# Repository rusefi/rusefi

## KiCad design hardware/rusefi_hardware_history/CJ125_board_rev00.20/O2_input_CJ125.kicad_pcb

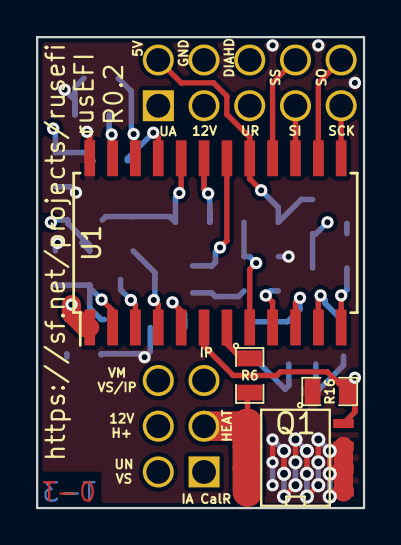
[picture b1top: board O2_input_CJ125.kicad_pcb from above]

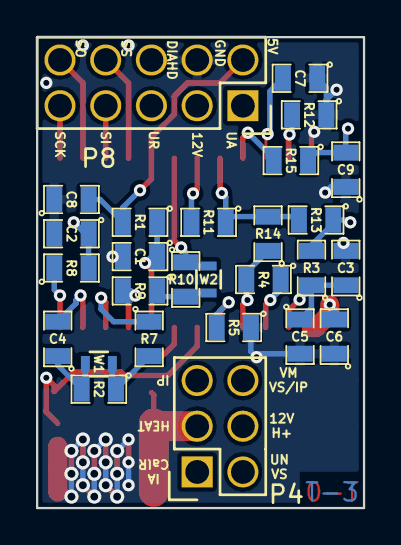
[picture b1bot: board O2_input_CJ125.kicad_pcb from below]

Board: 4 copper layers, 18.2 x 26.2 mm, 31 parts (27 on the bottom side), 31 nets.

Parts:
C1: 1000pF; SM0805
C2, C6, C8: 0.033uF; SM0805
C3, C4, C7: 0.1uF; SM0805
C5: 220pf; SM0805
C9: 0.01uF; SM0805
P4: CONN_02X03; Socket_Strip_Straight_2x03
P8: CONN_02X05; Socket_Strip_Straight_2x05
Q1: FDS2734; SO8E_ST
R1, R5, R7, R16: 10k; SM0805
R2: 21k6; SM0805
R3: 160; SM0805
R4: 61.9; SM0805
R6: 6.8k; SM0805
R8, R15: 1k; SM0805
R9: 82.5; SM0805
R10: 117.5; SM0805
R11: 4.7k; SM0805
R12, R13: 100k; SM0805
R14: 470k; SM0805
U1: CJ125; SOIC-24_7.5x15.4mm_Pitch1.27mm
W1, W2: TEST; R_0603

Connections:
/CF: C7.2, U1.22
/CJ125_5v: C8.2, P8.2, R1.2, U1.17
/CJ125_HEATER: P4.3, Q1.2, R6.2
/CJ125_IA: P4.1, R4.2, R14.1, U1.4
/CJ125_IP: P4.5, R4.1, U1.3
/CJ125_SCK: P8.9, U1.13
/CJ125_SI: P8.7, U1.15
/CJ125_SO: P8.10, U1.14
/CJ125_SS: P8.8, U1.16
/CJ125_UA: C9.2, P8.1, R15.1
/CJ125_UN: P4.2, R3.2, R13.1
/CJ125_UR: C2.1, P8.5, R8.2
/CJ125_VM: P4.6, R10.1, U1.18, W2.2
/CM: C4.2, U1.11
/DIAHD: R6.1, U1.7
/DIAHG: P8.6, Q1.1, R16.2, U1.6
/OSZ: R5.2, U1.5
/RF: R12.2, U1.23
/RM: R7.1, U1.10
/RS: R9.2, U1.9
/RST: C1.1, R1.1, U1.8
/UA: R15.2, U1.21
/UN: C3.1, C5.1, R3.1, U1.2
/UP: R11.1, R13.2, R14.2, U1.20
/UR: R8.1, U1.12
/US: R11.2, U1.19
/WO2-12V: C6.2, P4.4, P8.3, U1.1
GND: C1.2, C2.2, C3.2, C5.2, C6.1, C7.1, C8.1, C9.1, P8.4, Q1.3, R5.1, R12.1, R16.1, U1.24
unnamed: C4.1, R2.2, W1.1
unnamed: R2.1, R7.2, W1.2
unnamed: R9.1, R10.2, W2.1

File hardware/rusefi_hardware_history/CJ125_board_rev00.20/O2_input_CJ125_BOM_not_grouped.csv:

Reference, Value, Footprint, Datasheet, mfg,mfg#, vend1,vend1#
C7,0.1uF,SM0805,,avx,08055C104KAT2A,DIGI,478-1395-1-ND
R15,1k,SM0805,,Panasonic,ERA-6AEB102V,DIGI,P1.0KDACT-ND
R13,100k,SM0805,,vishay,CRCW0805100KFKEA,DIGI,541-100KCCT-ND
C9,0.01uF,SM0805,,avx,08055C103JAT2A,DIGI,478-3745-6-ND
C6,0.033uF,SM0805,,tdk,CGA4J2C0G1H333J125AA,DIGI,445-6950-1-ND
R8,1k,SM0805,,Panasonic,ERA-6AEB102V,DIGI,P1.0KDACT-ND
R4,61.9,SM0805,,vishay,CRCW080561R9FKEA,DIGI,541-61.9CCT-ND
R5,10k,SM0805,,BOURNS,CR0805-FX-1002ELF,DIGI,CR0805-FX-1002ELFCT-ND
C2,0.033uF,SM0805,,tdk,CGA4J2C0G1H333J125AA,DIGI,445-6950-1-ND
R12,100k,SM0805,,vishay,CRCW0805100KFKEA,DIGI,541-100KCCT-ND
C1,1000pF,SM0805,,avx,08052C102KAT2A ,DIGI,478-1339-1-ND
R6,6.8k,SM0805,,vishay,CRCW08056K80FKEA,DIGI,541-6.80KCCT-ND
C5,220pf,SM0805,,avx,08051A221JAT2A,DIGI,478-1286-1-ND
R1,10k,SM0805,,BOURNS,CR0805-FX-1002ELF,DIGI,CR0805-FX-1002ELFCT-ND
C4,0.1uF,SM0805,,avx,08055C104KAT2A,DIGI,478-1395-1-ND
R7,10k,SM0805,,BOURNS,CR0805-FX-1002ELF,DIGI,CR0805-FX-1002ELFCT-ND
R9,82.5,SM0805,,vishay,CRCW080582R5FKEA,DIGI,541-82.5CCT-ND
R14,470k,SM0805,,vishay,CRCW0805470KFKEA,DIGI,541-470KCCT-ND
R11,4.7k,SM0805,,vishay,CRCW08054K70FKEA,DIGI,541-4.70KCCT-ND
C8,0.033uF,SM0805,,tdk,CGA4J2C0G1H333J125AA,DIGI,445-6950-1-ND
U1,CJ125,SOIC-24_7.5x15.4mm_Pitch1.27mm,,bosh,CJ125-1267379259,future,1267379259
R10,117.5,SM0805,,Panasonic,ERJ-6ENF1180V,DIGI,P118CCT-ND
Q1,FDS2734,SO8E_ST,,ST,VNS14NV04,DIGI,497-11123-1-ND
W2,TEST,R_0603,,dnp,dnp,dnp,dnp
R2,21k6,SM0805,,vishay,CRCW080521K5FKEA,DIGI,541-21.5KCCT-ND
W1,TEST,R_0603,,dnp,dnp,dnp,dnp
R3,160,SM0805,,vishay,CRCW080561R9FKEA,DIGI,541-61.9CCT-ND
C3,0.1uF,SM0805,,avx,08055C104KAT2A,DIGI,478-1395-1-ND
P4,CONN_02X03,Socket_Strips:Socket_Strip_Straight_2x03,,dnp,dnp,dnp,dnp
P8,CONN_02X05,Socket_Strips:Socket_Strip_Straight_2x05,,dnp,dnp,dnp,dnp
R16,10k,SM0805,,BOURNS,CR0805-FX-1002ELF,DIGI,CR0805-FX-1002ELFCT-ND

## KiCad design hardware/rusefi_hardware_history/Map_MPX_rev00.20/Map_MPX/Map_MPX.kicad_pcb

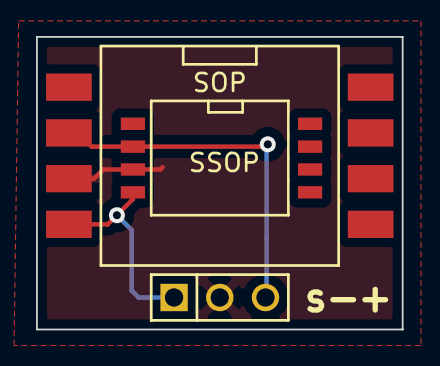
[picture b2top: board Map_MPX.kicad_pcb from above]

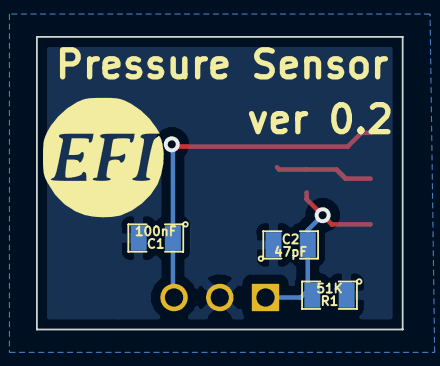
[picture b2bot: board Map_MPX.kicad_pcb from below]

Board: 2 copper layers, 20.3 x 16.3 mm, 4 parts (3 on the bottom side), 2 nets.

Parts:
C1: 100nF; SM0805
C2: 47pF; SM0805
R1: 51K; SM0805
SSOP: SOP; SSOP

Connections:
GND: C1.2, C2.1, R1.1
unnamed: C2.2, R1.2

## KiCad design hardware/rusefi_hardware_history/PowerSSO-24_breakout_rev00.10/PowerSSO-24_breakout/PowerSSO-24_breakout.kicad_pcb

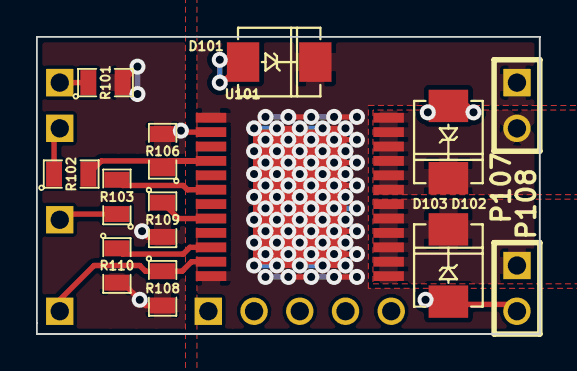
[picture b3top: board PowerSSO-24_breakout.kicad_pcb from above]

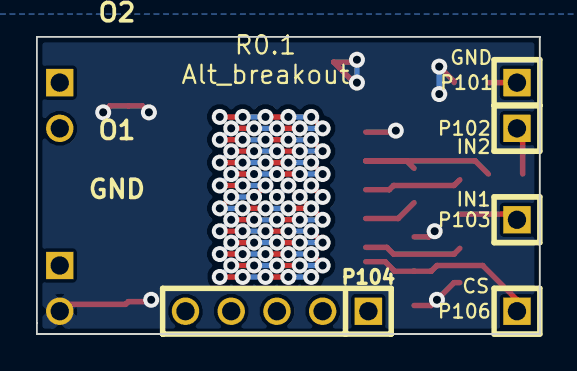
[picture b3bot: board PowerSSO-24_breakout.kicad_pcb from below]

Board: 2 copper layers, 27.9 x 16.5 mm, 18 parts (5 on the bottom side), 12 nets.

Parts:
D101, D102, D103: P6SMB36AT3G; DO-214AA(SMB)
P101, P102, P103, P106: CONN_1; SIL-1
P104: CONN_5; SIL-5
P107, P108: CONN_2; SIL-2
R101: TBD; SM0805
R102, R103, R106, R108: 10K; SM0805
R109, R110: 1K; SM0805
U101: VND5E025AKTR; PowerSSO-24

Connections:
/CS_DIS: P106.1, R108.1, U101.11
/I1: R109.1, U101.8
/I2: R110.1, U101.10
/IN1: R103.2, U101.6
/IN2: R102.2, R106.1, U101.4
/O1: D103.2, P108.1, U101.13, U101.14, U101.15, U101.16, U101.17, U101.18
/O2: D102.2, P107.2, U101.19, U101.20, U101.21, U101.22, U101.23, U101.24
/VCC: D101.2, P107.1, U101.1, U101.12, U101.EXP
GND: D101.1, D102.1, D103.1, P108.2, R101.2, R106.2, R108.2, R109.2, R110.2, U101.2
unnamed: P101.1, R101.1
unnamed: P103.1, R103.1
unnamed: P102.1, R102.1

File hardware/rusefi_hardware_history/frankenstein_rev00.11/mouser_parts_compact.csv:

### this file was generated by rusEfi bom_builder on Sat Mar 08 11:58:11 CST 2014
### 292 components in 2047 lines of frankenstein.cmp
### 65 kinds of components in input file
### 5 entries in BOM dictionary bom_dictionary_mouser.csv
### 0 entries in ignore list
### no BOM record for 1pin_CONN_1
### no BOM record for LED-0805_GREEN
### no BOM record for LED-0805_LED
### no BOM record for LED-0805_RED
### no BOM record for LED-1206_LED
### no BOM record for LOGO_F_LOGO
### no BOM record for LOGO_LOGO
### no BOM record for MICRO-SDCARD-CONNECTOR-3300060P1_MICRO-SDCARD-CONNECTOR-3300060P1
### no BOM record for OSTVN06A150_CONN_6
### no BOM record for PIN_ARRAY-6X1_CONN_6
### no BOM record for PIN_ARRAY_10X2_CONN_10X2
### no BOM record for PIN_ARRAY_10X2_M_CONN_10X2
### no BOM record for PIN_ARRAY_1_CONN_1
### no BOM record for PIN_ARRAY_2X1_CONN_2
### no BOM record for PIN_ARRAY_2_A_CONN_2
### no BOM record for PIN_ARRAY_2_A_JUMPER
### no BOM record for PIN_ARRAY_3X1_CONN_3
### no BOM record for PIN_ARRAY_3_A_CONN_3
### no BOM record for PIN_ARRAY_4x1_CONN_4
### no BOM record for PIN_ARRAY_5x2_CONN_5X2
### no BOM record for SIL-16_3.5MM_CONN_16
### no BOM record for SIL-2_0R
### no BOM record for SIL-2_CONN_2
### no BOM record for SIL-2_DIODE
### no BOM record for SIL-2_JUMPER
### no BOM record for SIL-2_OPT
### no BOM record for SIL-2_TEST
### no BOM record for SM0805_.1uF
### no BOM record for SM0805_0.01uF
### no BOM record for SM0805_0.1uF
### no BOM record for SM0805_100
### no BOM record for SM0805_1000pF
### no BOM record for SM0805_10K
### no BOM record for SM0805_10k
### no BOM record for SM0805_10uF
### no BOM record for SM0805_120
### no BOM record for SM0805_1500
### no BOM record for SM0805_1K
### no BOM record for SM0805_1M
### no BOM record for SM0805_1k
### no BOM record for SM0805_1uF
### no BOM record for SM0805_20K
### no BOM record for SM0805_20R
### no BOM record for SM0805_2700
### no BOM record for SM0805_4.7uF
### no BOM record for SM0805_4700pF
### no BOM record for SM0805_47pF
### no BOM record for SM0805_500K
### no BOM record for SM0805_5k
### no BOM record for SM0805_LED
### no BOM record for SM1206_LED
### no BOM record for SO8E_ST_OVP_DRIVER
### no BOM record for SOD-123_DIODE
### no BOM record for bornier3_CONN_3
### no BOM record for msoic-8_TC4427AVOA
### no BOM record for pin_array_10x2_CONN_10X2
### no BOM record for pin_array_3x2_CONN_3X2
### no BOM record for pin_array_4x2_CONN_4X2
### no BOM record for sot23_DOUBLE_SCHOTTKY
### no BOM record for uMAX-uSOP_10_MAX9939




1,656-DX2R005HN2E700,mini USB socket
1,296-11654-1-ND,CAN driver
1,700-MAX9926UAEE,VR chip
3,595-LMV324IDR,quad op-amp
1,895-FT232RL,USB TTL chip

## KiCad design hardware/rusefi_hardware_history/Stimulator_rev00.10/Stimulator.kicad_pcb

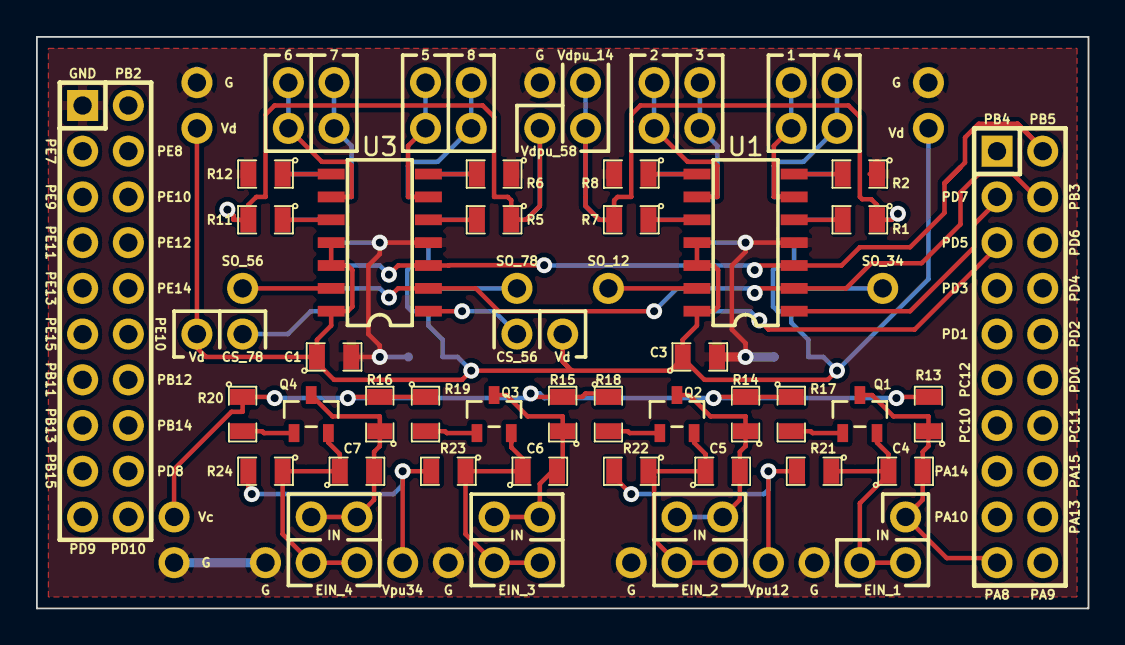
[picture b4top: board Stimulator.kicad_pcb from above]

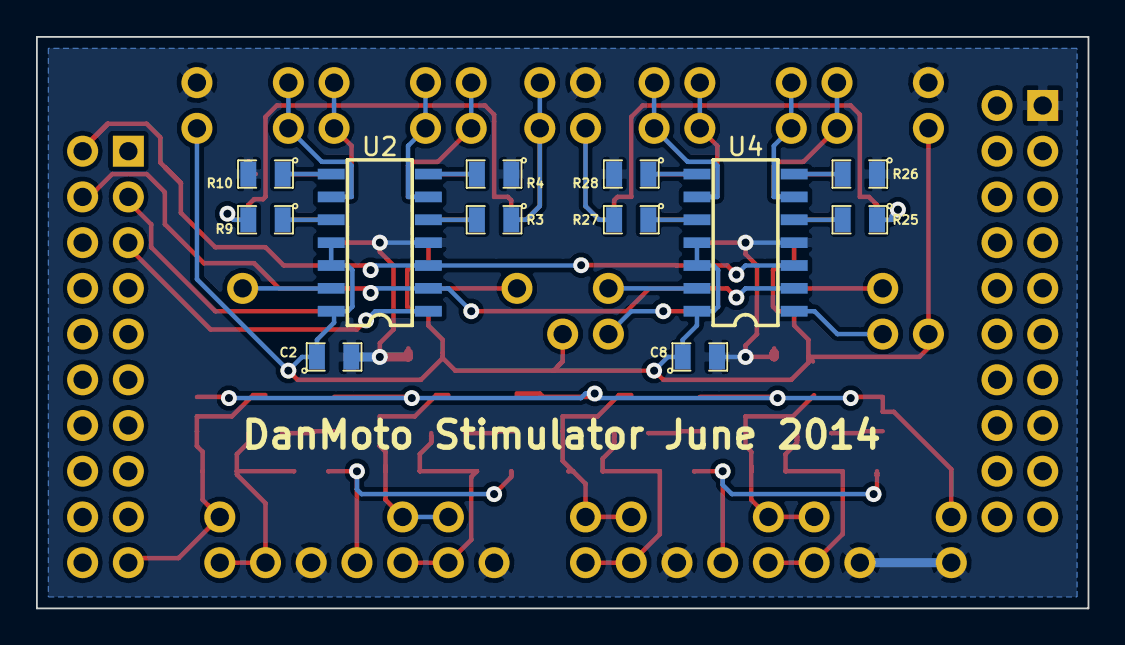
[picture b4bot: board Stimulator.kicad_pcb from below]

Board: 2 copper layers, 58.4 x 31.8 mm, 101 parts (12 on the bottom side), 53 nets.

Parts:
C1, C2, C3, C8: 0.1uF; SM0805
C4, C5, C6, C7: 100 pF; SM0805
P1, P3, P4, P5, P6, P7, P8, P9, P10, P11, P12, P13, P14, P15, P16, P17, P18, P19, P20, P21, P22, P23, P24, P25, P26, P27, P28, P29, P30, P31, P32, P33, P34, P35, P36, P38, P39, P40, P41, P42, P43, P44, P45, P46, P47, P48, P49, P50, P51, P52, P53, P54, P55, P56, P57: CONN_1; 1PIN_A
P2, P37: CONN_10X2; Pin_Header_Straight_2x10
Q1, Q2, Q3, Q4: 2N7002; sot23
R1, R2, R3, R4, R5, R6, R7, R8, R9, R10, R11, R12, R25, R26, R27, R28: 0; SM0805
R13, R14, R15, R16, R17, R18, R19, R20, R21, R22, R23, R24: 10k; SM0805
U1, U2, U3, U4: MCP42010; SOIC-14_Narrow

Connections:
/CS_12: P37.3, U1.1
/CS_34: P37.5, U2.1
/CS_56: P45.1, U3.1
/CS_78: P46.1, U4.1
/EIN_1: C4.1, P28.1, P29.1, Q1.2, R21.1
/EIN_2: C5.1, P30.1, P31.1, Q2.2, R22.1
/EIN_3: C6.1, P32.1, P33.1, Q3.2, R23.1
/EIN_4: C7.1, P34.1, P35.1, Q4.2, R24.1
/IN_1: C4.2, P20.1, P37.19, Q1.3, R13.1
/IN_2: C5.2, P21.1, P22.1, Q2.3, R14.1
/IN_3: C6.2, P23.1, P24.1, Q3.3, R15.1
/IN_4: C7.2, P25.1, P26.1, Q4.3, R16.1
/MOSI: P37.2, U1.3, U2.3, U3.3, U4.3
/OUT1: P4.1, P5.1, U1.6
/OUT2: P14.1, P15.1, U1.9
/OUT3: P6.1, P7.1, U2.6
/OUT4: P16.1, P17.1, U2.9
/OUT5: P8.1, P9.1, U3.6
/OUT6: P18.1, P19.1, U3.9
/OUT7: P47.1, P48.1, U4.6
/OUT8: P50.1, P51.1, U4.9
/SCK: P37.4, U1.2, U2.2, U3.2, U4.2
/Vc: P27.1, R13.2, R14.2, R15.2, R16.2, R17.1, R18.1, R19.1, R20.1
/Vd: C1.1, C2.1, C3.1, C8.1, P13.1, P53.1, P55.1, P56.1, U1.11, U1.12, U1.14, U2.11, U2.12, U2.14, U3.11, U3.12, U3.14, U4.11, U4.12, U4.14
/Vdpu_14: P3.1, P57.1, R1.1, R3.1, R7.2, R9.2
/Vdpu_58: P52.1, R5.1, R11.2, R25.1, R27.2
/Vipu12: P36.1, R21.2, R22.2
/Vipu34: P54.1, R23.2, R24.2
GND: C1.2, C2.2, C3.2, C8.2, P1.1, P2.1, P38.1, P39.1, P40.1, P41.1, P42.1, P43.1, P44.1, R2.1, R4.1, R6.1, R8.2, R10.2, R12.2, R26.1, R28.2, U1.4, U2.4, U3.4, U4.4
unnamed: P10.1, U1.13
unnamed: P11.1, U2.13
unnamed: P12.1, U3.13
unnamed: P49.1, U4.13
unnamed: Q1.1, R17.2
unnamed: Q2.1, R18.2
unnamed: Q3.1, R19.2
unnamed: Q4.1, R20.2
unnamed: R1.2, U1.5
unnamed: R2.2, U1.7
unnamed: R3.2, U2.5
unnamed: R4.2, U2.7
unnamed: R5.2, U3.5
unnamed: R6.2, U3.7
unnamed: R7.1, U1.10
unnamed: R8.1, U1.8
unnamed: R9.1, U2.10
unnamed: R10.1, U2.8
unnamed: R11.1, U3.10
unnamed: R12.1, U3.8
unnamed: R25.2, U4.5
unnamed: R26.2, U4.7
unnamed: R27.1, U4.10
unnamed: R28.1, U4.8

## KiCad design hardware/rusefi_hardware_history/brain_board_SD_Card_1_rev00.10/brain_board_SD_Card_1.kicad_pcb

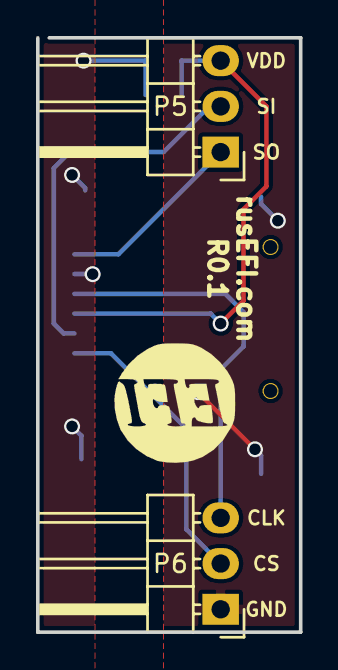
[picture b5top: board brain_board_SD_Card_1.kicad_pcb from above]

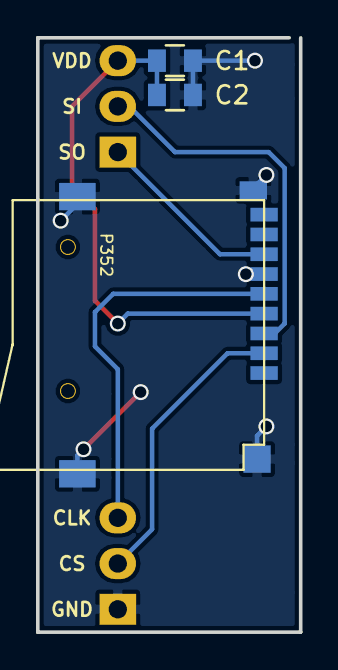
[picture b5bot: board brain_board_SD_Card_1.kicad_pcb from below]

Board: 2 copper layers, 14.6 x 33.0 mm, 6 parts (3 on the bottom side), 6 nets.

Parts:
C1: 1000pF; C_0805
C2: 0.1uF; C_0805
G1: LOGO; LOGO_F
P5, P6: CONN_01X03; Pin_Header_Angled_1x03
P352: MICRO-SDCARD-CONNECTOR-3300060P1

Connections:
/3.3V: C1.2, C2.2, P5.3, P352.4
/CS_SD_MODULE: P6.2, P352.2
/SPI_MISO: P5.1, P352.7
/SPI_MOSI: P5.2, P352.3
/SPI_SCK: P6.3, P352.5
GND: C1.1, C2.1, P6.1, P352.6, P352.G1, P352.G2, P352.G3, P352.G4

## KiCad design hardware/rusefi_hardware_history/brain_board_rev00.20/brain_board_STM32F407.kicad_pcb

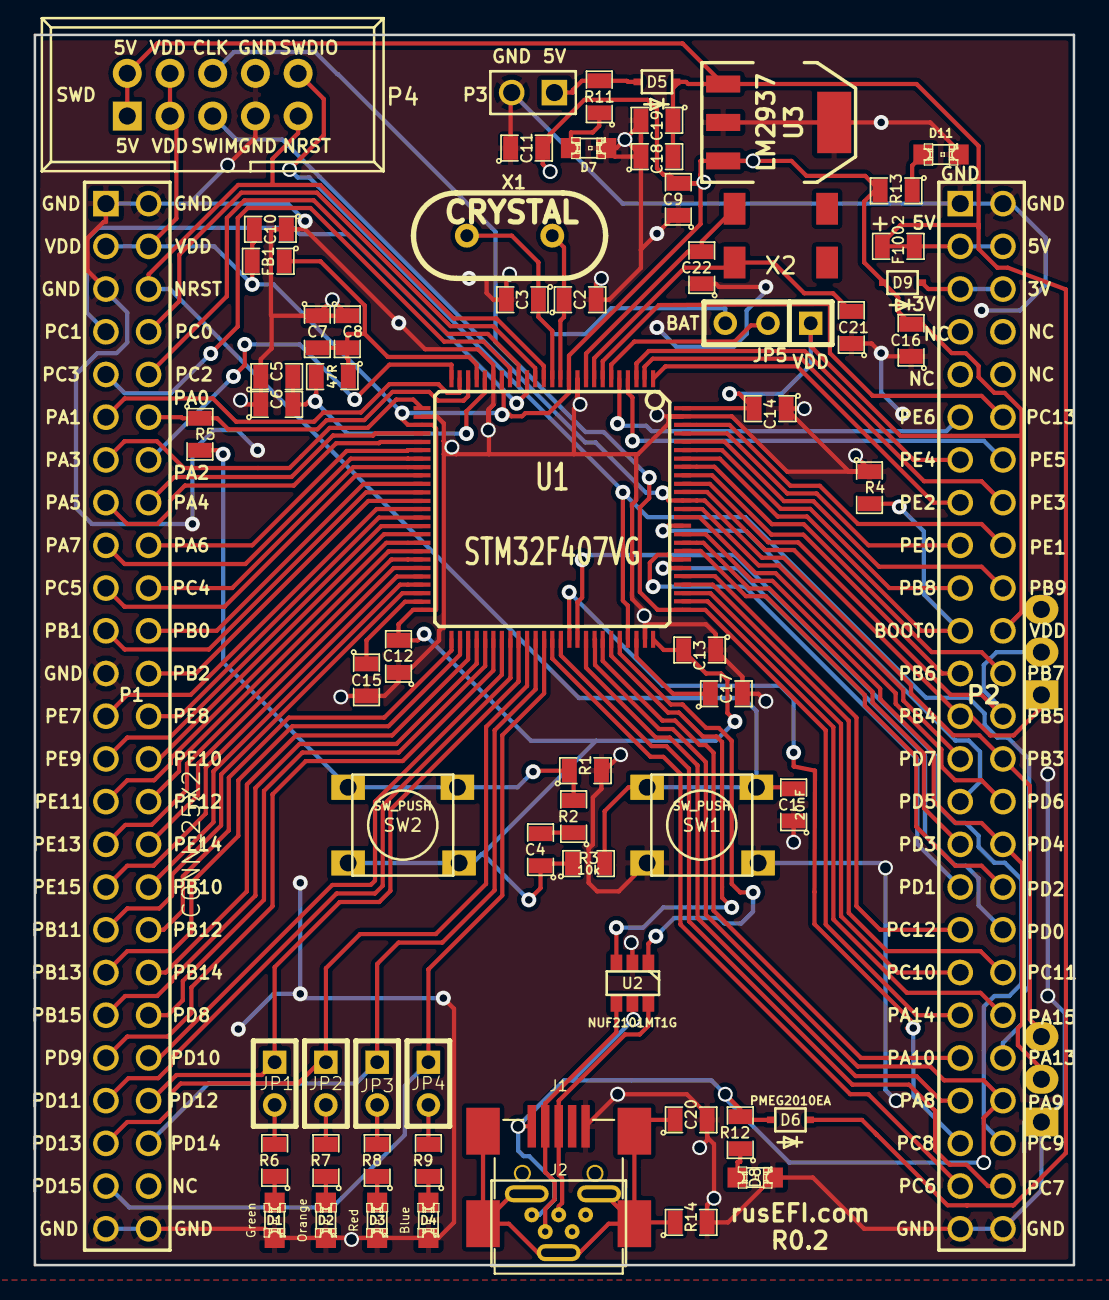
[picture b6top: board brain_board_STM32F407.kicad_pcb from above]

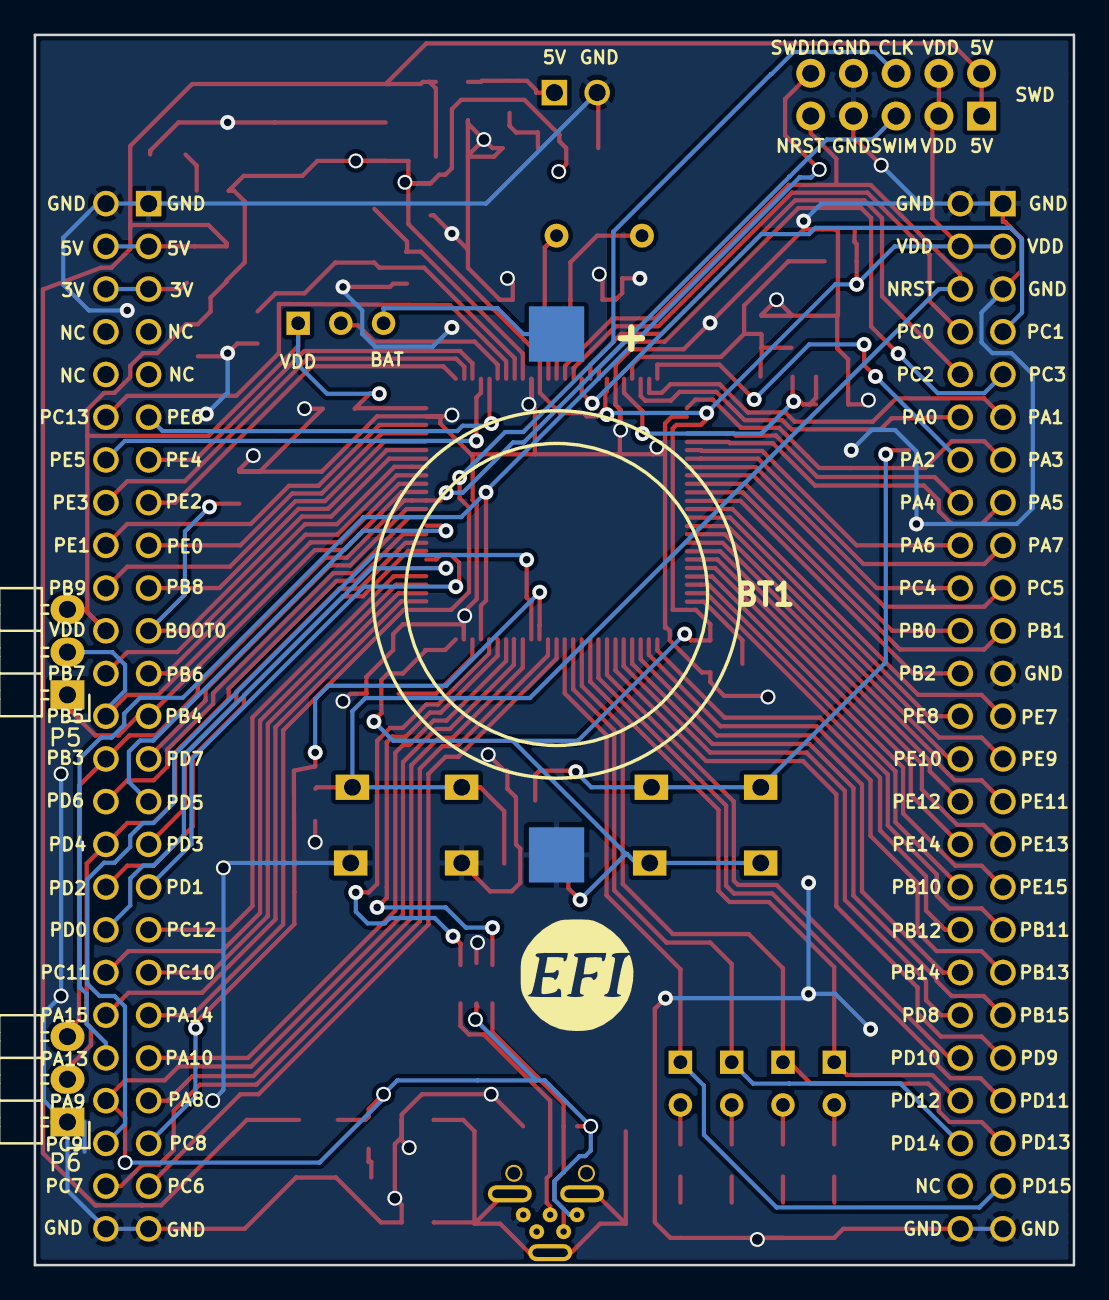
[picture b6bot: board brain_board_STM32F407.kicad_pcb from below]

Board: 2 copper layers, 61.8 x 73.2 mm, 70 parts (4 on the bottom side), 111 nets.

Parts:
BT1: BATTERY_CR2032; BATT_CR2032_MPD
C1: 20nF; SM0805
C2, C3, C21, C22: 18pF; SM0805
C4, C15, C17: 2u2F; SM0805
C5, C8: 0.01uF; SM0805
C6, C7, C16: 1uF; SM0805
C9, C10, C11, C12, C13, C14, C18, C20: 0.1uF; SM0805
C19: 4.7uF; SM0805
D1, D2, D3, D4, D7, D8, D11: BLUE_LED_0805; LED-0805_A
D5, D6, D9: PMEG2010EA; SOD-323
F1002: FUSE; SM0805-diode
FB1: FILTER; SM0805
G1: LOGO; LOGO_F
J1: MINI-USB-5P-3400020P1
J2: MINI-USB-5P-3400020P1V; MINI-USB_RCTP_V-T_B
JP1, JP2, JP3, JP4: JUMPER; JUMPER-2
JP5: JUMPER3; SIL-3
P1, P2: CONN_25X2; PIN_ARRAY_25x2_A
P3: CONN_2; PIN_ARRAY_2_A
P4: CONN_02X05; IDC_Header_Straight_10pins
P5, P6: CONN_01X03; Pin_Header_Angled_1x03
R1, R3, R4: 10k; SM0805
R2: 100R; SM0805
R5: 330R; SM0805
R6, R7, R8, R9: 680R; SM0805
R10: 47R; SM0805
R11, R12, R13: 1k; SM0805
R14: 100k; SM0805
SW1, SW2: SW_PUSH; TL-1105
U1: STM32F407VG; TQFP_100
U2: NUF2101MT1G; SOT-457
U3: LM2937; SOT223
X1: CRYSTAL; HC-49V
X2: CRYSTAL(MC306); MC-306

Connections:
/3V: D9.2, P2.5, P2.6
/5V: C18.2, C19.1, D5.2, D6.2, F1002.1, F1002.2, P2.3, P2.4, P4.1, P4.2, U3.1
/BOOT0: P2.21, R4.2, U1.94
/D+: J1.3, J2.3, U2.6
/D-: J1.2, J2.2, U2.4
/NRST: C1.2, P1.6, P4.9, R3.2, SW1.1, U1.14
/PA0: P1.12, R5.1, U1.23
/PA1: P1.11, U1.24
/PA2: P1.14, U1.25
/PA3: P1.13, U1.26
/PA4: P1.16, U1.29
/PA5: P1.15, U1.30
/PA6: P1.18, U1.31
/PA7: P1.17, U1.32
/PA8: P2.43, U1.67
/PA9: D6.1, J1.1, J2.1, P2.44, R12.2, U1.68, U2.5
/PA10: P2.41, U1.69
/PA11: U1.70, U2.3
/PA12: U1.71, U2.1
/PA13: P2.42, P4.10, U1.72
/PA14: P2.39, P4.6, U1.76
/PA15: P2.40, U1.77
/PB0: P1.22, U1.35
/PB1: P1.21, U1.36
/PB2: P1.24, U1.37
/PB3: P2.28, P4.5, P6.3, U1.89
/PB4: P2.25, P5.1, U1.90
/PB5: P2.26, P5.2, U1.91
/PB6: P2.23, U1.92
/PB7: P2.24, U1.93
/PB8: P2.19, U1.95
/PB9: P2.20, U1.96
/PB10: P1.34, U1.47
/PB11: P1.35, U1.48
/PB12: P1.36, U1.51
/PB13: P1.37, U1.52
/PB14: P1.38, U1.53
/PB15: P1.39, U1.54
/PC0: P1.8, U1.15
/PC1: P1.7, U1.16
/PC2: P1.10, U1.17
/PC3: P1.9, U1.18
/PC4: P1.20, U1.33
/PC5: P1.19, U1.34
/PC6: P2.47, U1.63
/PC7: P2.48, U1.64
/PC8: P2.45, U1.65
/PC9: P2.46, U1.66
/PC10: P2.37, U1.78
/PC11: P2.38, U1.79
/PC12: P2.35, U1.80
/PC13: P2.12, U1.7
/PD0: P2.36, U1.81
/PD1: P2.33, U1.82
/PD2: P2.34, U1.83
/PD3: P2.31, U1.84
/PD4: P2.32, P6.2, U1.85
/PD5: P2.29, U1.86
/PD6: P2.30, U1.87
/PD7: P2.27, U1.88
/PD8: P1.40, U1.55
/PD9: P1.41, U1.56
/PD10: P1.42, U1.57
/PD11: P1.43, U1.58
/PD12: JP1.1, P1.44, U1.59
/PD13: JP2.1, P1.45, U1.60
/PD14: JP3.1, P1.46, U1.61
/PD15: JP4.1, P1.47, U1.62
/PE0: P2.17, U1.97
/PE1: P2.18, U1.98
/PE2: P2.15, U1.1
/PE3: P2.16, U1.2
/PE4: P2.13, U1.3
/PE5: P2.14, U1.4
/PE6: P2.11, U1.5
/PE7: P1.25, U1.38
/PE8: P1.26, U1.39
/PE9: P1.27, U1.40
/PE10: P1.28, U1.41
/PE11: P1.29, U1.42
/PE12: P1.30, U1.43
/PE13: P1.31, U1.44
/PE14: P1.32, U1.45
/PE15: P1.33, U1.46
/Shield: C20.1, J1.6, J2.6, R14.1
/VDD: C4.1, C9.2, C10.2, C11.2, C12.2, C13.2, C14.2, C16.2, D9.1, FB1.2, JP5.1, P1.3, P1.4, P2.22, P4.3, P4.4, P5.3, R3.1, R13.2, SW2.2, U1.11, U1.19, U1.28, U1.50, U1.75, U1.100, U3.3
GND: BT1.2, C1.1, C2.2, C3.2, C5.1, C6.1, C7.1, C8.1, C9.1, C10.1, C11.1, C12.1, C13.1, C14.1, C15.2, C16.1, C17.2, C18.1, C19.2, C20.2, C21.1, C22.1, D1.2, D2.2, D3.2, D4.2, D7.2, D8.2, D11.2, J1.5, J2.5, P1.1, P1.2, P1.5, P1.23, P1.49, P1.50, P2.1, P2.2, P2.49, P2.50, P3.2, P4.7, P4.8, P6.1, R1.2, R4.1, R14.2, SW1.2, U1.10, U1.20, U1.27, U1.74, U1.99, U2.2, U3.2, U3.4
unnamed: BT1.1, JP5.3
unnamed: C2.1, U1.12, X1.2
unnamed: C3.1, U1.13, X1.1
unnamed: C4.2, R2.1
unnamed: C5.2, C6.2, R10.2, U1.21
unnamed: C7.2, C8.2, FB1.1, R10.1, U1.22
unnamed: C15.1, U1.49
unnamed: C17.1, U1.73
unnamed: C21.2, U1.8, X2.1
unnamed: C22.2, U1.9, X2.4
unnamed: D1.1, R6.1
unnamed: D2.1, R7.1
unnamed: D3.1, R8.1
unnamed: D4.1, R9.1
unnamed: D5.1, P3.1, R11.2
unnamed: D7.1, R11.1
unnamed: D8.1, R12.1
unnamed: D11.1, R13.1
unnamed: JP1.2, R6.2
unnamed: JP2.2, R7.2
unnamed: JP3.2, R8.2
unnamed: JP4.2, R9.2
unnamed: JP5.2, U1.6
unnamed: R1.1, R2.2, R5.2, SW2.1
